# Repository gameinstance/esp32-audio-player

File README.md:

# esp32-audio-player - GameInstance.com

A PCM56 stereo player powered by ESP32.

Follow the instructions on the [Firmware](./firmware) page to build the code, then flash it onto the
[Hardware](./hardware).

Further details on: https://gameinstance.com/post/106/ESP32-PCM56-player

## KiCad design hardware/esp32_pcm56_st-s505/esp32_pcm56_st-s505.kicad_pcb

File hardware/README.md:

# esp32-audio-player - GameInstance.com

An ESP32 audio player powered by PCM56 DAC chips.

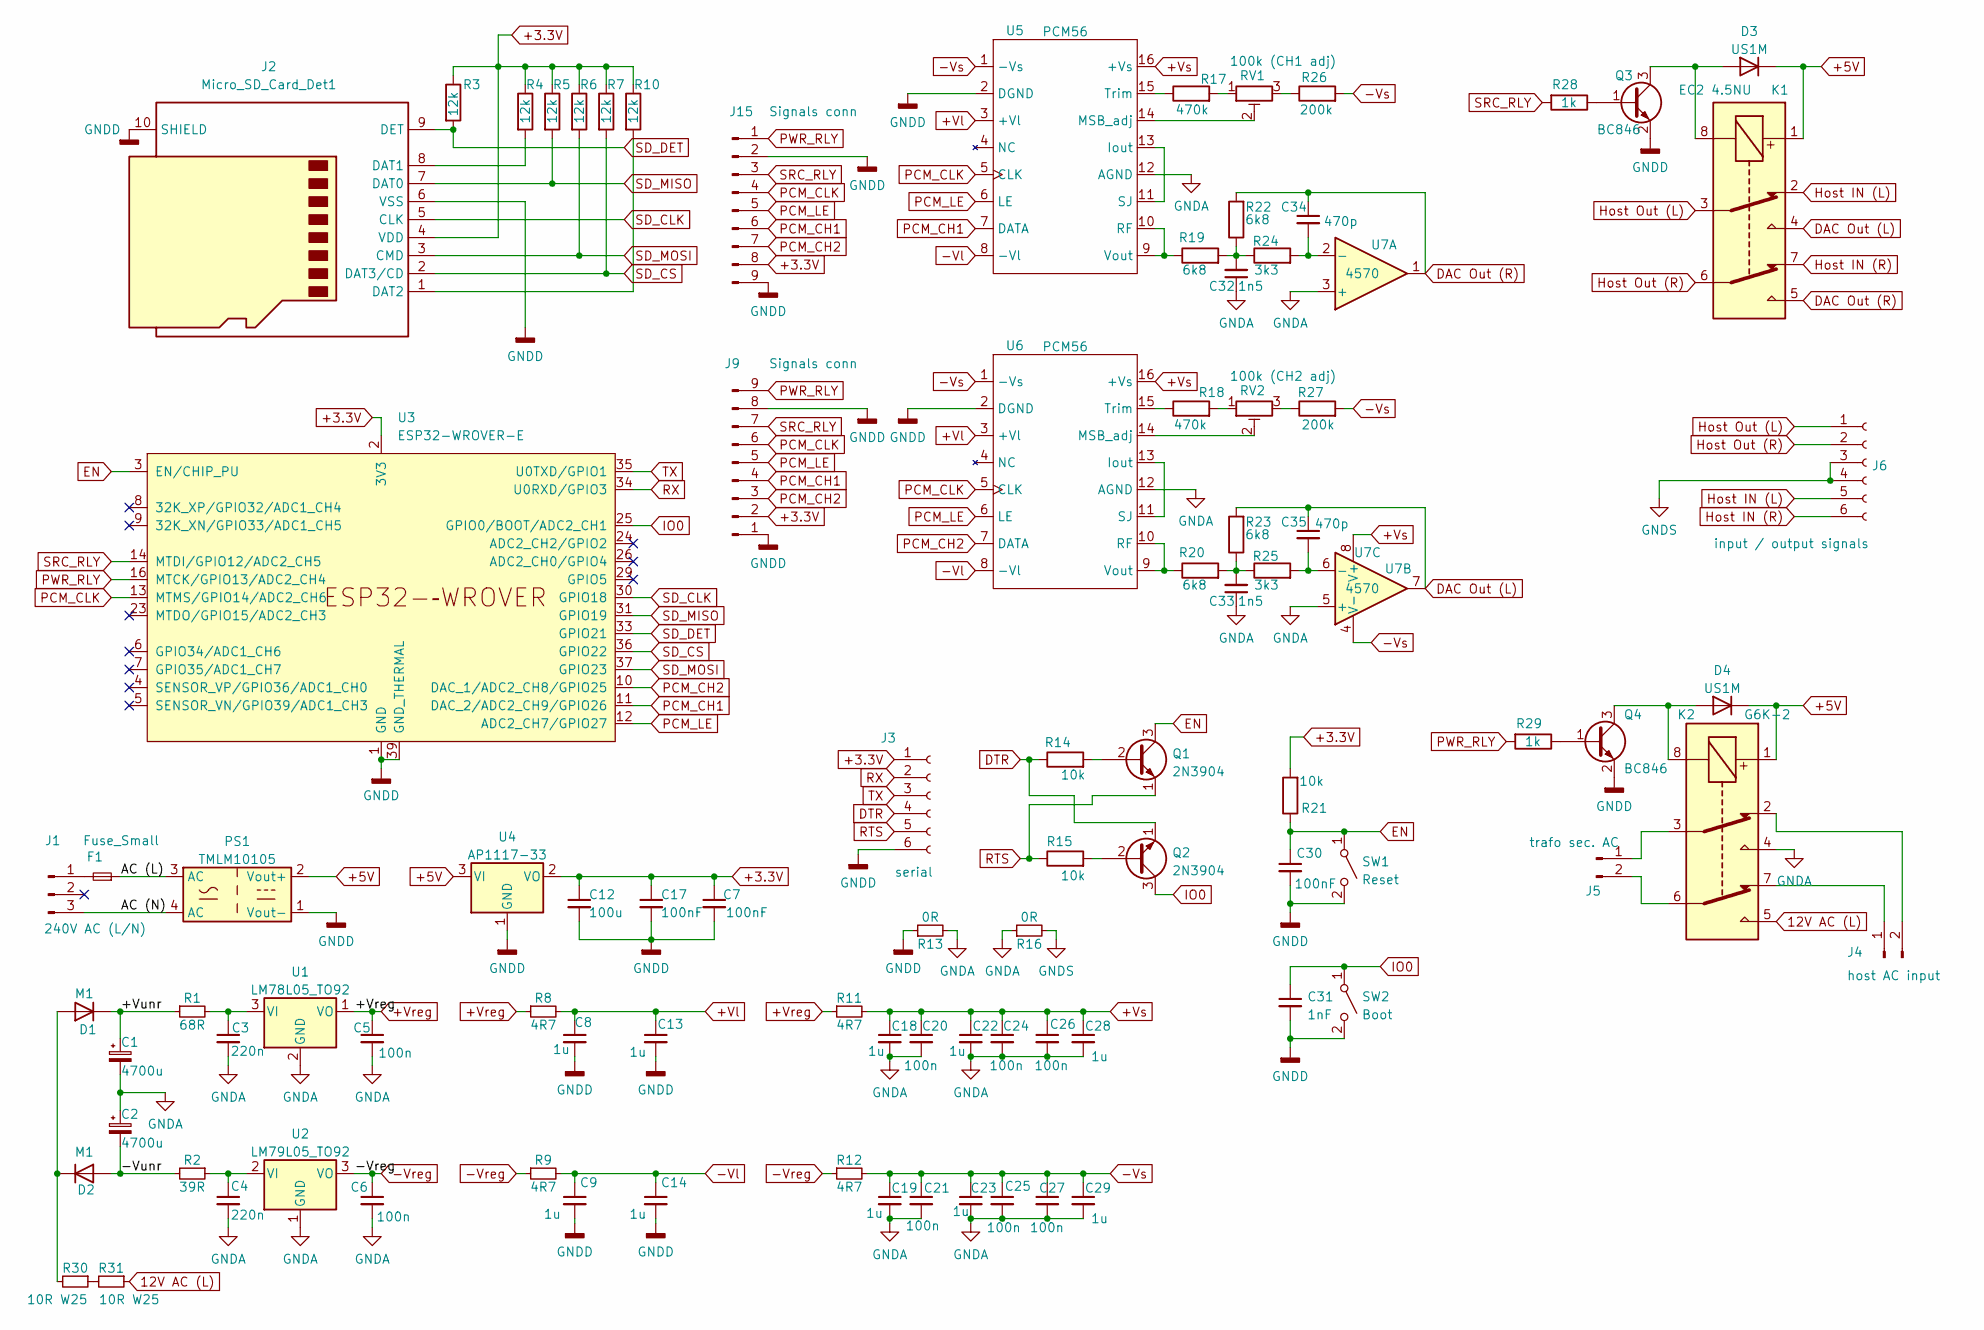
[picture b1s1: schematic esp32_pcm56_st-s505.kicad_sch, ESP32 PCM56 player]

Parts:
C1, C2: 4700u; C_Radial_D18.0mm_H35.5mm_P7.50mm
C3, C4: 220n; C_0805_2012Metric
C5, C6, C20, C21, C24, C25, C26, C27: 100n; C_1206_3216Metric
C7, C17, C30: 100nF; C_1206_3216Metric
C8, C9, C13, C14, C18, C19, C22, C23, C28, C29: 1u; C_1206_3216Metric
C12: 100u; C_1210_3225Metric
C31: 1nF; C_1206_3216Metric
C32, C33: 1n5; C_0805_2012Metric
C34, C35: 470p; C_0805_2012Metric
D1, D2: M1; D_SMA
D3, D4: US1M; D_SMA
F1: Fuse_Small; Fuse_Littelfuse_395Series
J1: 240V AC (L/N); Molex_KK-254_AE-6410-03A_1x03_P2.54mm_Vertical
J2: Micro_SD_Card_Det1; CTF-11081-P
J3: serial; PinSocket_1x06_P2.54mm_Vertical
J4: host AC input; Molex_KK-254_AE-6410-02A_1x02_P2.54mm_Vertical
J5: trafo sec. AC; Molex_KK-254_AE-6410-02A_1x02_P2.54mm_Vertical
J6: input / output signals; PinSocket_1x06_P2.54mm_Vertical
J9: Signals conn; PinHeader_1x09_P2.54mm_Horizontal
J15: Signals conn; PinSocket_1x09_P2.54mm_Vertical
K1: EC2 4.5NU; Relay_2P2T_10x6mm_TE_IMxxG
K2: G6K-2; Relay_2P2T_10x6mm_TE_IMxxG
PS1: TMLM10105; RPDZN E10W
Q1, Q2: 2N3904; TSOT-23
Q3, Q4: BC846; SOT-23
R1: 68R; R_1206_3216Metric
R2: 39R; R_1206_3216Metric
R3, R4, R5, R6, R7, R10: 12k; R_0603_1608Metric
R8, R9, R11, R12: 4R7; R_1206_3216Metric
R13: 0R; R_Axial_DIN0207_L6.3mm_D2.5mm_P10.16mm_Horizontal
R14, R15, R21: 10k; R_0805_2012Metric
R16: 0R; R_1206_3216Metric
R17, R18: 470k; R_0805_2012Metric
R19, R20, R22, R23: 6k8; R_0805_2012Metric
R24, R25: 3k3; R_0805_2012Metric
R26, R27: 200k; R_0805_2012Metric
R28, R29: 1k; R_0805_2012Metric
R30, R31: 10R W25; R_1206_3216Metric
RV1: 100k (CH1 adj); Potentiometer_Bourns_3296W_Vertical
RV2: 100k (CH2 adj); Potentiometer_Bourns_3296W_Vertical
SW1: Reset; SW_PUSH_6mm_H5mm
SW2: Boot; SW_PUSH_6mm_H5mm
U1: LM78L05_TO92; TO-92_Inline
U2: LM79L05_TO92; TO-92_Inline
U3: ESP32-WROVER-E
U4: AP1117-33; SOT-223-3_TabPin2
U5, U6: PCM56; DIP-16_W7.62mm
U7: 4570; DIP-8_W7.62mm

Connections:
12V AC (L): K2.5, R31.1
+3.3V: C7.1, C12.1, C17.1, J2.4 (VDD), J3.1, J9.2, J15.8, R3.1, R4.1, R5.1, R6.1, R7.1, R10.1, R21.2, U3.2 (3V3), U4.2 (VO)
+5V: D3.1 (K), D4.1 (K), K1.1, K2.1, PS1.2 (Vout+), U4.3 (VI)
+Vl: C8.1, C13.1, R8.2, U5.3 (+Vl), U6.3 (+Vl)
+Vreg: C5.1, R8.1, R11.1, U1.1 (VO)
+Vs: C18.1, C20.1, C22.1, C24.1, C26.1, C28.1, R11.2, U5.16 (+Vs), U6.16 (+Vs), U7.8 (V+)
-Vl: C9.1, C14.1, R9.2, U5.8 (-Vl), U6.8 (-Vl)
-Vreg: C6.1, R9.1, R12.1, U2.3 (VO)
-Vs: C19.1, C21.1, C23.1, C25.1, C27.1, C29.1, R12.2, R26.2, R27.2, U5.1 (-Vs), U6.1 (-Vs), U7.4 (V-)
/+Vunr: C1.1, D1.1 (K), R1.1
/-Vunr: C2.2, D2.2 (A), R2.2
/AC (L): F1.1, PS1.3 (AC)
/AC (N): J1.3, PS1.4 (AC)
DAC Out (L): C35.1, K1.4, R23.2, U7.7
DAC Out (R): C34.1, K1.5, R22.2, U7.1
DTR: J3.4, Q2.1 (E), R14.1
EN: C30.1, Q1.3 (C), R21.1, SW1.1 (A), U3.3 (EN/CHIP_PU)
GNDA: C1.2, C2.1, C3.2, C4.2, C5.2, C6.2, C18.2, C19.2, C20.2, C21.2, C22.2, C23.2, C24.2, C25.2, C26.2, C27.2, C28.2, C29.2, C32.1, C33.1, K2.4, R13.2, R16.1, U1.2 (GND), U2.1 (GND), U5.12 (AGND), U6.12 (AGND), U7.3 (+), U7.5 (+)
GNDD: C7.2, C8.2, C9.2, C12.2, C13.2, C14.2, C17.2, C30.2, C31.2, J2.6 (VSS), J2.10 (SHIELD), J3.6, J9.1, J9.8, J15.2, J15.9, PS1.1 (Vout-), Q3.2 (E), Q4.2 (E), R13.1, SW1.2 (B), SW2.2 (B), U3.1 (GND), U3.15 (GND), U3.38 (GND), U3.39 (GND_THERMAL), U4.1 (GND), U5.2 (DGND), U6.2 (DGND)
GNDS: J6.3, J6.4, R16.2
Host IN (L): J6.5, K1.2
Host IN (R): J6.6, K1.7
Host Out (L): J6.1, K1.3
Host Out (R): J6.2, K1.6
IO0: C31.1, Q2.3 (C), SW2.1 (A), U3.25 (GPIO0/BOOT/ADC2_CH1)
unnamed: C32.2, R19.2, R22.1, R24.1
unnamed: C33.2, R20.2, R23.1, R25.1
unnamed: D1.2 (A), D2.1 (K), R30.2
unnamed: D3.2 (A), K1.8, Q3.3 (C)
unnamed: D4.2 (A), K2.8, Q4.3 (C)
unnamed: F1.2, J1.1
unnamed: J2.8 (DAT1), R4.2
unnamed: J2.1 (DAT2), R10.2
unnamed: J4.1, K2.7
unnamed: J4.2, K2.2
unnamed: J5.1, K2.3
unnamed: J5.2, K2.6
unnamed: Q1.2 (B), R14.2
unnamed: Q2.2 (B), R15.2
unnamed: Q3.1 (B), R28.1
unnamed: Q4.1 (B), R29.1
unnamed: R17.2, RV1.1
unnamed: R18.2, RV2.1
unnamed: R26.1, RV1.3
unnamed: R27.1, RV2.3
unnamed: R30.1, R31.2
unnamed: C3.1, R1.2, U1.3 (VI)
unnamed: C4.1, R2.1, U2.2 (VI)
unnamed: U5.11 (SJ), U5.13 (Iout)
unnamed: RV1.2, U5.14 (MSB_adj)
unnamed: R19.1, U5.9 (Vout), U5.10 (RF)
unnamed: R17.1, U5.15 (Trim)
unnamed: U6.11 (SJ), U6.13 (Iout)
unnamed: RV2.2, U6.14 (MSB_adj)
unnamed: R20.1, U6.9 (Vout), U6.10 (RF)
unnamed: R18.1, U6.15 (Trim)
unnamed: C34.2, R24.2, U7.2 (-)
unnamed: C35.2, R25.2, U7.6 (-)
PCM_CH1: J9.4, J15.6, U3.11 (DAC_2/ADC2_CH9/GPIO26), U5.7 (DATA)
PCM_CH2: J9.3, J15.7, U3.10 (DAC_1/ADC2_CH8/GPIO25), U6.7 (DATA)
PCM_CLK: J9.6, J15.4, U3.13 (MTMS/GPIO14/ADC2_CH6), U5.5 (CLK), U6.5 (CLK)
PCM_LE: J9.5, J15.5, U3.12 (ADC2_CH7/GPIO27), U5.6 (LE), U6.6 (LE)
PWR_RLY: J9.9, J15.1, R29.2, U3.16 (MTCK/GPIO13/ADC2_CH4)
RTS: J3.5, Q1.1 (E), R15.1
RX: J3.2, U3.34 (U0RXD/GPIO3)
SD_CLK: J2.5 (CLK), U3.30 (GPIO18)
SD_CS: J2.2 (DAT3/CD), R7.2, U3.36 (GPIO22)
SD_DET: J2.9 (DET), R3.2, U3.33 (GPIO21)
SD_MISO: J2.7 (DAT0), R5.2, U3.31 (GPIO19)
SD_MOSI: J2.3 (CMD), R6.2, U3.37 (GPIO23)
SRC_RLY: J9.7, J15.3, R28.2, U3.14 (MTDI/GPIO12/ADC2_CH5)
TX: J3.3, U3.35 (U0TXD/GPIO1)

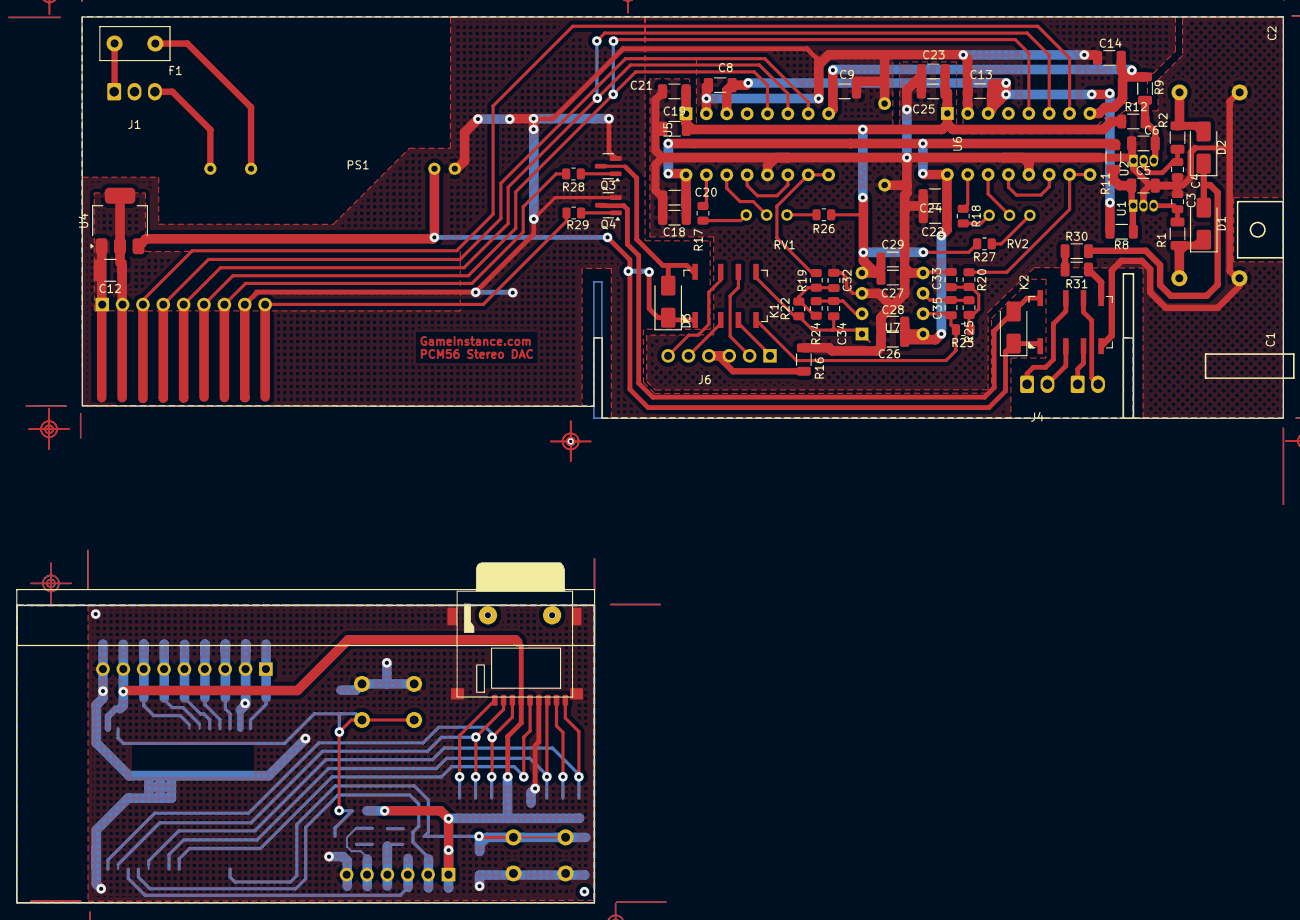
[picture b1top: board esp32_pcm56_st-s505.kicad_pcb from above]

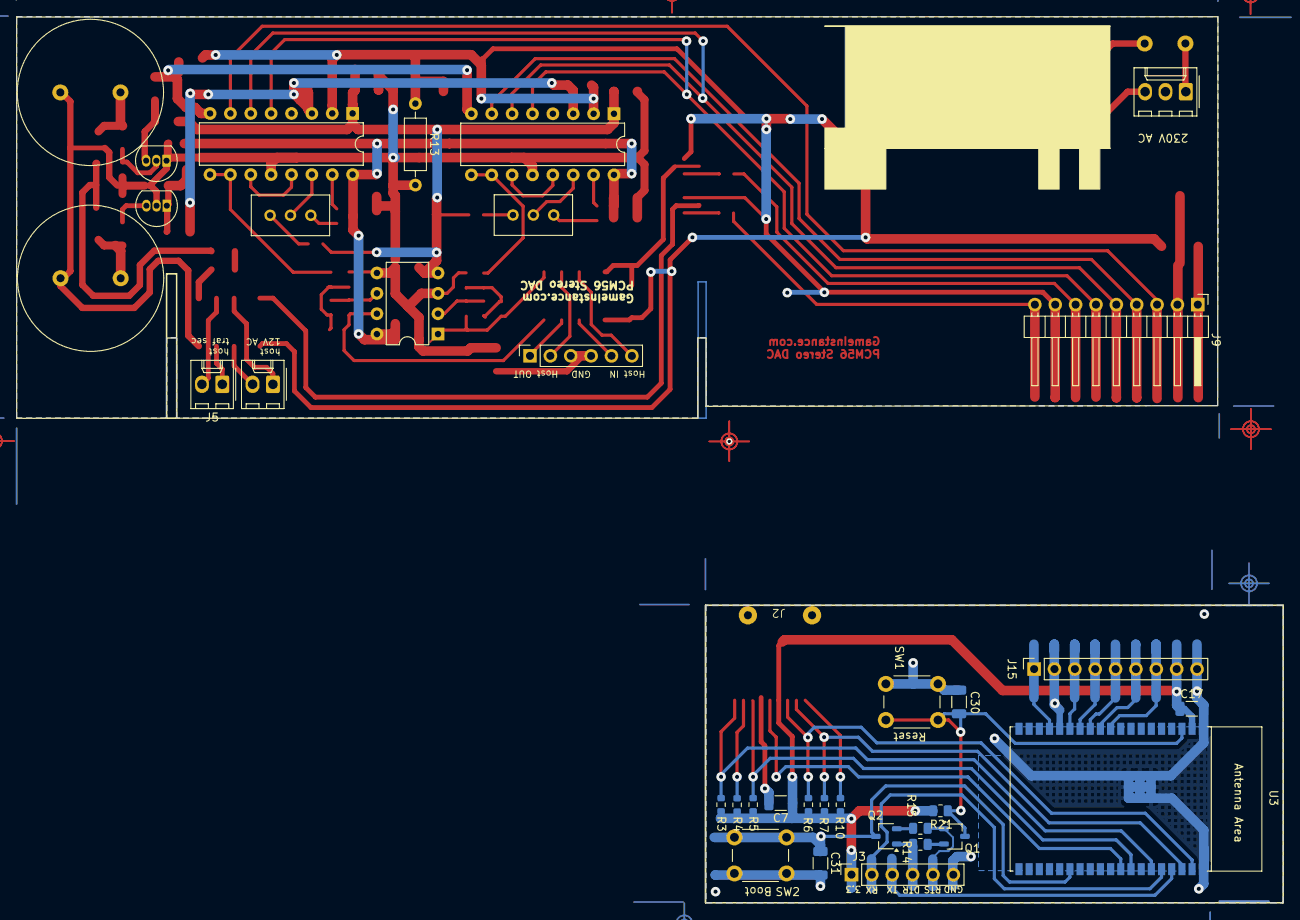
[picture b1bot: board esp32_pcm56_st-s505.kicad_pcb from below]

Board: 2 copper layers, 157.9 x 110.5 mm, 93 parts (36 on the bottom side), 72 nets.

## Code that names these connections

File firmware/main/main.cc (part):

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
//      SPI       GPIO    SD     SDSPI  MMC
// ----------------------------------------
#define SD_CS     22   // DAT3   CS     RES
#define SD_SCK    18   // CLK    SCLK   CLK
#define SD_MOSI   23   // CMD    DI     CMD
#define SD_MISO   19   // DAT0   DO     DAT
#define SD_DET    21   // xxx    xxx    xxx

#define PCM_CLK       14
#define PCM_LE        27
#define PCM_CH1_DATA  26
#define PCM_CH2_DATA  25

#define SRC_RLY  12
#define PWR_RLY  13

static const unsigned char wifi_ssid[32] = "WIFI_AP";
static const unsigned char wifi_pasw[64] = "WIFI_PASS";
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
auto bus_config = esp::io::spi_bus_config{
	.sck_pin  = SD_SCK,  // SD#CLK,
	.mosi_pin = SD_MOSI, // SD#CMD,
	.miso_pin = SD_MISO, // SD#DAT0,
	.quadwp_pin = -1,    // SD#DAT2,
	.quadhd_pin = -1,    // SD#DAT3,
	.max_transfer_size = buffer_max_size,
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};
auto sd_config = esp::io::spi_sd_config{
	.spi_bus = bus_config,
	.cs_pin = SD_CS,
};
auto player_config = stereo_player_config {
	.clk_gpio      = PCM_CLK,
	.ch1_data_gpio = PCM_CH1_DATA,
	.ch2_data_gpio = PCM_CH2_DATA,
	.le_gpio       = PCM_LE,
};
auto relays_config = pcm56_player::relays_output_config {
	.source_gpio = SRC_RLY,
	.power_gpio = PWR_RLY,
};
auto card_detect_config = pcm56_player::card_detect_input_config {
	.gpio = SD_DET,
};

auto player_buffer = player_buffer_type{};
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
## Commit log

2024-08-09 added LICENSE.md and README.md
2024-08-09 added hardware dir w/ LICENSE.md, README.md and logo.svg
2024-09-16 firmware: corrected player behavior ...
    * removed redundant state updates in prepare_next_track();
    * reduced the scope of the player to minimize fs I/O overlap effects;
    * improved logging for http UI requests;
    * corrected and reduced verbosity for player timer log entries.
2024-09-16 hardware: added KiCAD project files for the technics st-s505 implementation
2024-09-16 Update README.md
    added rendered preview of DAC board implementation for Technics ST-S505
2024-10-01 firmware: corrected rule of 5
2024-10-02 firmware: corrected rule of 3/5 on player and buffer modules

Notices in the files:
firmware/main/main.cc:
Copyright (C) 2024  Bogdan-Gabriel Alecu  (GameInstance.com)
This library is free software: you can redistribute it and/or modify it under the terms of the
GNU General Public License as published by the Free Software Foundation, either version 3 of the
License, or (at your option) any later version.
